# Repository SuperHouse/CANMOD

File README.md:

Fully Isolated CAN Bus Module
=============================

Copyright 2024 SuperHouse Automation Pty Ltd  [www.superhouse.tv]()

CAN bus module with an SPI interface and a fully-isolated transceiver and dual power
rails, allowing full-range CAN voltage when driven with a 3.3V microcontroller. The
transceiver is rated to 70V isolation on bus faults, protecting the microcontroller
from extreme transient voltages.

This module was designed as a building block for rapidly creating Test Modules for
the [Testomatic PCB Test Jig System](https://github.com/superhouse/testomatic). It
allows the tester to communicate with a target Device Under Test via CAN bus. However,
there is nothing specific about Testomatic in this module so it can be used for any
project that requires an isolated on non-isolated CAN controller and transceiver.

## Features
* MCP2515 CAN Controller
* ISO1042 isolated CAN Transceiver
* Split GND for logic and bus isolation if required
* Compatible with MCU logic levels from 1.7V to 5.5V
* Onboard CAN termination

CAN termination is enabled by default, via a cut-track jumper at the top right of the
module labelled "TERM". To disable termination, cut the small track between the solder
pads. The track can be bridged again later with solder if required.

CAN termination is provided by a high-power 120R resistor, rated to withstand a dead
short between either of the CAN bus lines and 12V vehicle power.

## Pinout
* **VCCL**: Logic voltage to suit the connected microcontroller. Maximum range 1.7V - 5.5V
* **!INT**: Interrupt output from MCP2515 CAN controller (active low)
* **SCK**: SPI Clock input
* **MOSI**: SPI MOSI input
* **MISO**: SPI MISO output
* **!CS**: SPI chip select (active low)
* **!RST**: Reset input (active low, with onboard pullup)
* **GNDL**: Logic-side GND
* **VCCC**: CAN-side supply voltage. Nominal 5V
* **H**: CAN High
* **L**: CAN Low
* **GNDC**: CAN-side GND

GNDL and GNDC are isolated on the module, with full galvanic isolation provided by the transceiver. In typical installations without full isolation, these two GNDs can be connected together.

When running from a 5V MCU and isolation is not required, both VCCL and VCCC can be supplied from the same power rail. This removes the galvanic isolation between the bus and the controller.

## Installation
Schematic and PCB were created in Fusion360 and exported as EAGLE format,
which can be imported back into Fusion360 or various other packages including KiCAD.

## Credits
Designed by Jonathan Oxer <jon@oxer.com.au>.

## Distribution
The specific terms of distribution of this project are governed by the
license referenced below.

## License
Licensed under the TAPR Open Hardware License (www.tapr.org/OHL).
The "license" folder within this repository also contains a copy of
this license in plain text format.

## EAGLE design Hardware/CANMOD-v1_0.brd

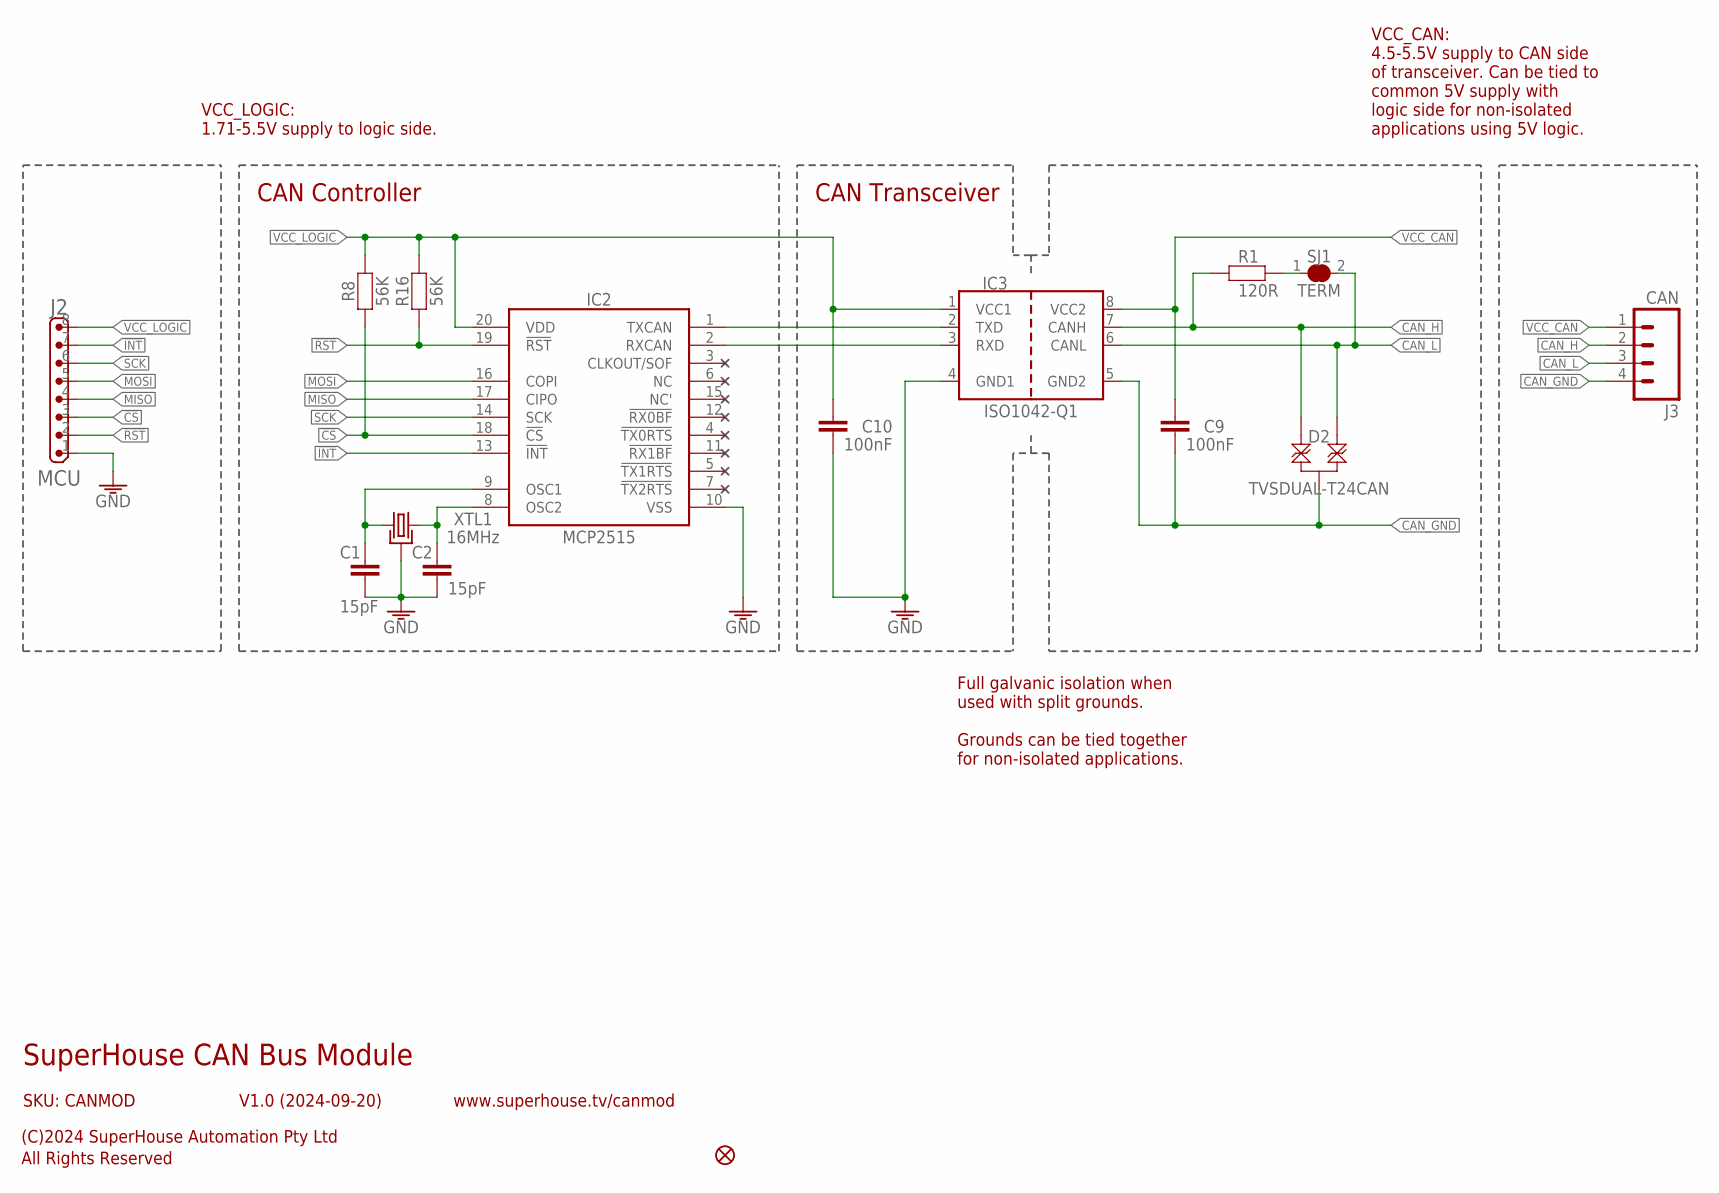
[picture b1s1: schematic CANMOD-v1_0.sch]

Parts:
C1, C2: 15pF; C0603
C9, C10: 100nF; C0603
D2: TVSDUAL-T24CAN; SOT23-3
FID1: FIDUCIAL1X2.5; FIDUCIAL-1X2.5
IC2: SN65HVD231DR; TSSOP20
IC3: ISO1042-Q1; SO08-W
J2: MCU; 1X08
J3: CAN; 1X04
R1: 120R; R2010
R8, R16: 56K; R0603
SJ1: TERM; SJC
XTL1: 16MHz; CRYSTAL-SMD-3X2

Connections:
!CS: IC2.18 (!CS), J2.3, R8.1
!INT: IC2.13 (!INT), J2.7
!RST: IC2.19 (!RST), J2.2, R16.1
CAN_GND: C9.2, D2.3, IC3.5 (GND2), J3.4
CAN_H: D2.2, IC3.7 (CANH), J3.2, R1.1
CAN_L: D2.1, IC3.6 (CANL), J3.3, SJ1.2
GND: C1.2, C2.2, C10.2, IC2.10 (VSS), IC3.4 (GND1), J2.1, XTL1.2 (GND), XTL1.4 (GND)
MISO: IC2.17 (CIPO), J2.4
MOSI: IC2.16 (COPI), J2.5
unnamed: R1.2, SJ1.1
unnamed: IC2.1 (TXCAN), IC3.2 (TXD)
unnamed: IC2.2 (RXCAN), IC3.3 (RXD)
unnamed: C2.1, IC2.8 (OSC2), XTL1.3 (2)
unnamed: C1.1, IC2.9 (OSC1), XTL1.1
SCK: IC2.14 (SCK), J2.6
VCC_CAN: C9.1, IC3.8 (VCC2), J3.1
VCC_LOGIC: C10.1, IC2.20 (VDD), IC3.1 (VCC1), J2.8, R8.2, R16.2

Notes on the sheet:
SuperHouse CAN Bus Module
V1.0 (2024-09-20)
SKU: CANMOD
(C)2024 SuperHouse Automation Pty Ltd
All Rights Reserved
www.superhouse.tv/canmod
CAN Transceiver
CAN Controller
Full galvanic isolation when used with split grounds. Grounds can be tied together for non-isolated applications.
VCC_CAN: 4.5-5.5V supply to CAN side of transceiver. Can be tied to common 5V supply with logic side for non-isolated applications using 5V logic.
VCC_LOGIC: 1.71-5.5V supply to logic side.

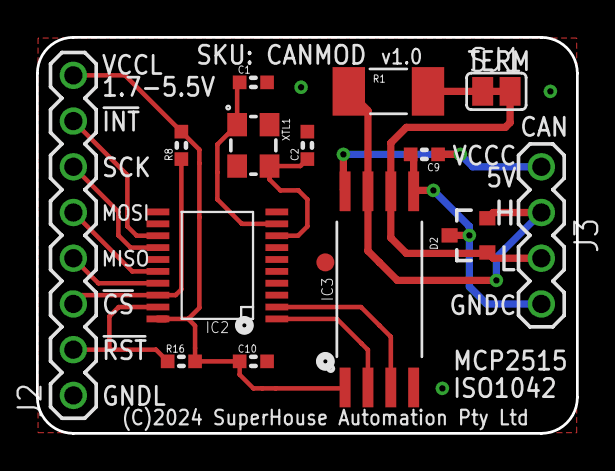
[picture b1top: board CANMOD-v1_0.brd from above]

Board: 2 copper layers, 30.0 x 22.0 mm, 15 parts (0 on the bottom side), 17 nets.

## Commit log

2025-02-24 Initial import of project.
2025-02-24 Added explanation of CAN termination scheme.
2025-02-24 Added gitignore
